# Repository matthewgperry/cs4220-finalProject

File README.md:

# Real-Time Embedded Systems (CS 4220/6235) Final Project - Fall 2024

## Overview

This repository contains the hardware schematics (PCB design files) in `occupancySensorBoard`, the initial Arduino scripts in `arduino`, and the ESP32 firmware in `firmware`.

The firmware defines an occupancy sensor with the DFRobot C4001 MM-Wave sensor with the Matter standard.

## Setup

Note: The ESP-IDF has an unresolved bug, requiring a manual workaround. The bug I experienced is described [here](https://esp32.com/viewtopic.php?t=42744).

1. Choose an install method for the ESP-IDF. I used the Linux install method. Follow the instructions [here](https://docs.espressif.com/projects/esp-idf/en/v5.3.1/esp32/get-started/index.html).

2. Install [ESP-Matter](https://docs.espressif.com/projects/esp-matter/en/latest/esp32/developing.html).

3. Clone this repository.

4. Source the ESP-IDF and ESP-Matter environment variables.

5. Navigate to the `firmware` directory.

6. Run `idf.py set-target esp32c6` to set the target board to the ESP32-C6.

7. Run `idf.py menuconfig` to configure the firmware (WiFi setup, flash size, etc).

8. Run `idf.py build` to build the firmware.

## PCB Production

The PCB design files are in the `occupancySensorBoard` directory. The PCB was designed in KiCad.

The PCB was produced by JLCPCB. The Gerber, BOM, and CPL files are in the `occupancySensorBoard/jlcpcb` directory.

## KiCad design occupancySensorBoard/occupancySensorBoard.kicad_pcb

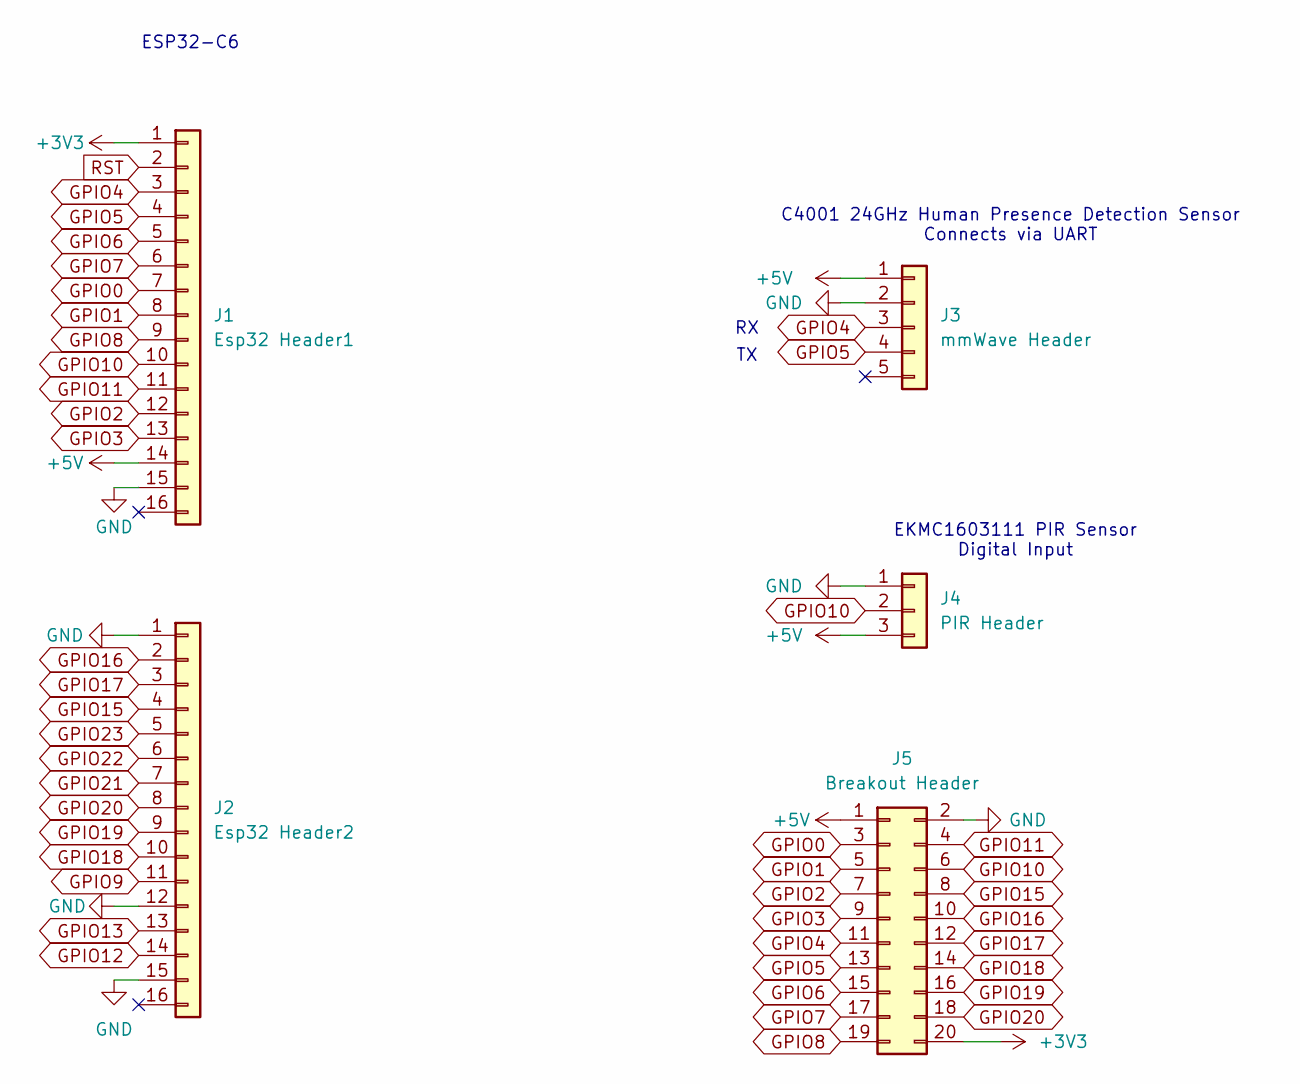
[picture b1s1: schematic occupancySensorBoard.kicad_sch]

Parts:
J1: Esp32 Header1; PinHeader_1x16_P2.54mm_Vertical
J2: Esp32 Header2; PinHeader_1x16_P2.54mm_Vertical
J3: mmWave Header; PinHeader_1x05_P2.54mm_Vertical
J4: PIR Header; 917-47-103-41005000
J5: Breakout Header; PinHeader_2x10_P2.54mm_Vertical

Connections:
+3V3: J1.1, J5.20
+5V: J1.14, J3.1, J4.3, J5.1
GND: J1.15, J2.1, J2.12, J2.15, J3.2, J4.1, J5.2
GPIO0: J1.7, J5.3
GPIO1: J1.8, J5.5
GPIO2: J1.12, J5.7
GPIO3: J1.13, J5.9
GPIO4: J1.3, J3.3, J5.11
GPIO5: J1.4, J3.4, J5.13
GPIO6: J1.5, J5.15
GPIO7: J1.6, J5.17
GPIO8: J1.9, J5.19
GPIO9: J2.11
GPIO10: J1.10, J4.2, J5.6
GPIO11: J1.11, J5.4
GPIO12: J2.14
GPIO13: J2.13
GPIO15: J2.4, J5.8
GPIO16: J2.2, J5.10
GPIO17: J2.3, J5.12
GPIO18: J2.10, J5.14
GPIO19: J2.9, J5.16
GPIO20: J2.8, J5.18
GPIO21: J2.7
GPIO22: J2.6
GPIO23: J2.5
RST: J1.2

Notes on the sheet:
C4001 24GHz Human Presence Detection Sensor Connects via UART
EKMC1603111 PIR Sensor Digital Input
ESP32-C6

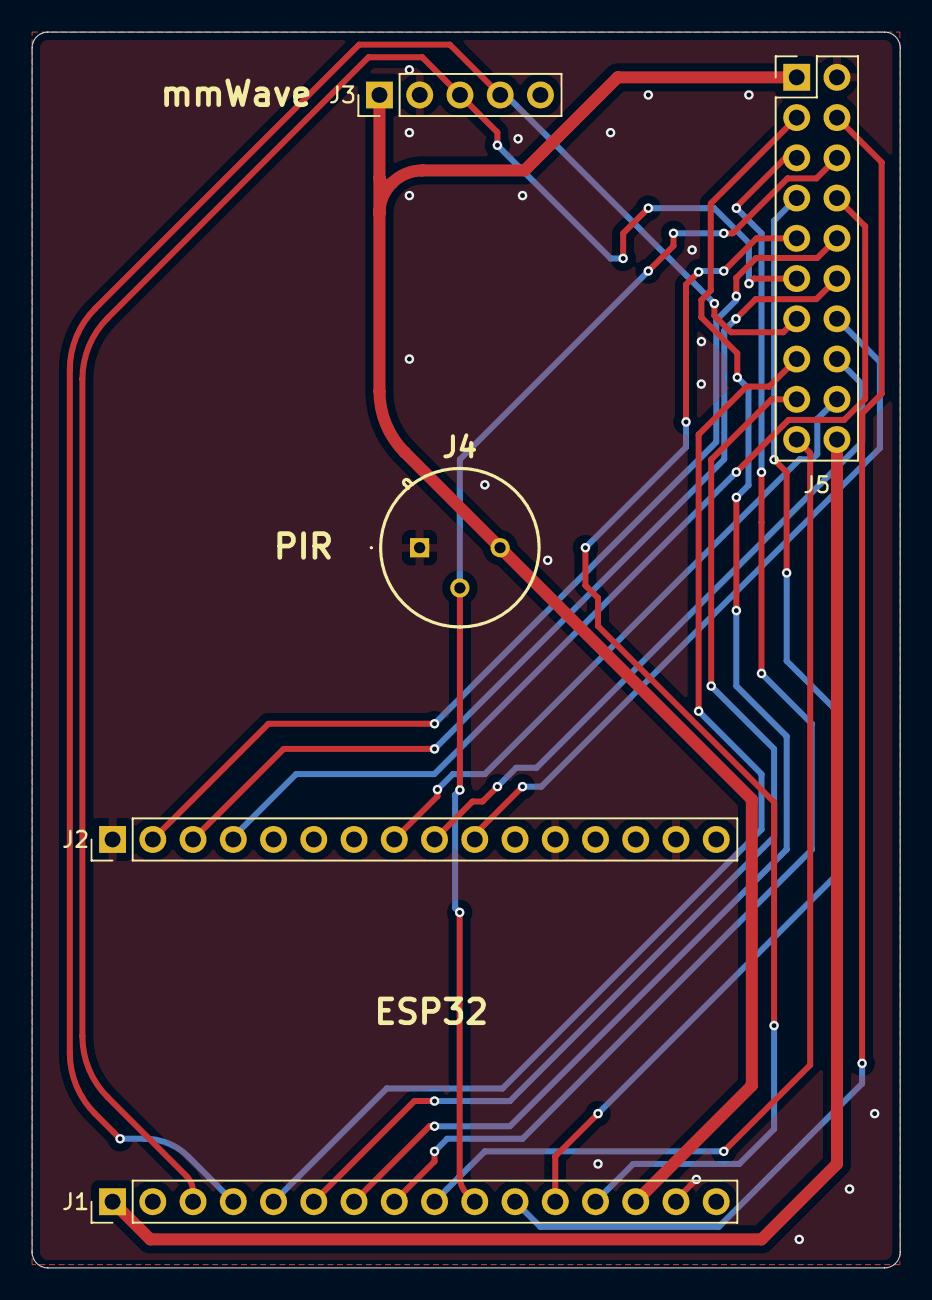
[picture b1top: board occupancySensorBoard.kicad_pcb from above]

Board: 2 copper layers, 54.8 x 78.0 mm, 5 parts (0 on the bottom side), 20 nets.

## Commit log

2024-10-18 Initial commit, add PCB and Arduino sensor tests
2024-11-29 Add ESP firmware
2024-11-29 Add README
